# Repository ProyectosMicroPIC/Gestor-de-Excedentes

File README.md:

Con este Gestor de Excedentes completamente DIY podrás derivar tus excedentes fotovoltaicos a cualquier electrodoméstico (resistivo) que tengas en casa, aprovechando la energía sobrante de la mejor manera.

En el vídeo te explico cómo está hecho y cómo funciona.

https://youtu.be/Iet8Q6aDYok

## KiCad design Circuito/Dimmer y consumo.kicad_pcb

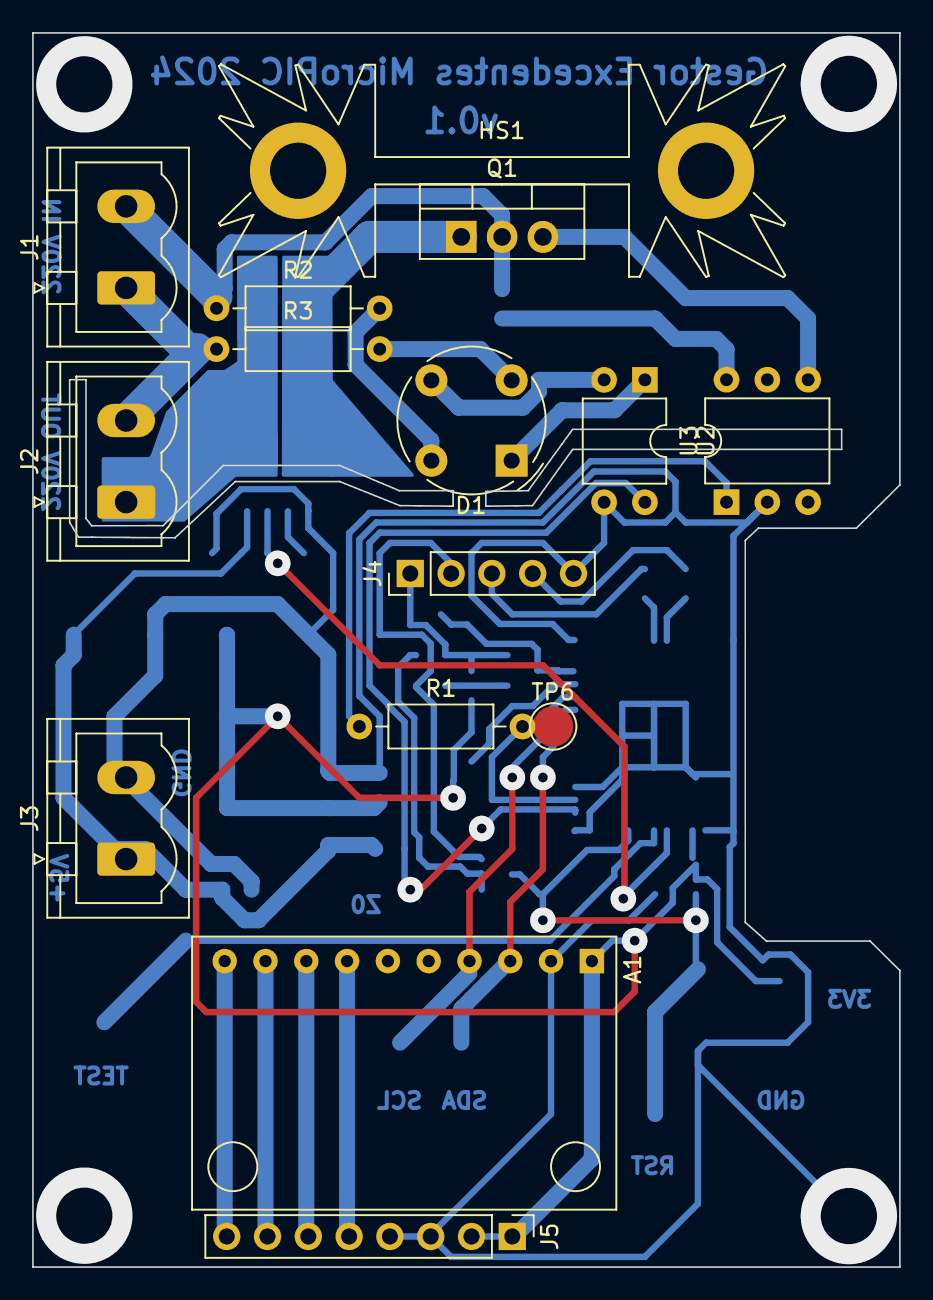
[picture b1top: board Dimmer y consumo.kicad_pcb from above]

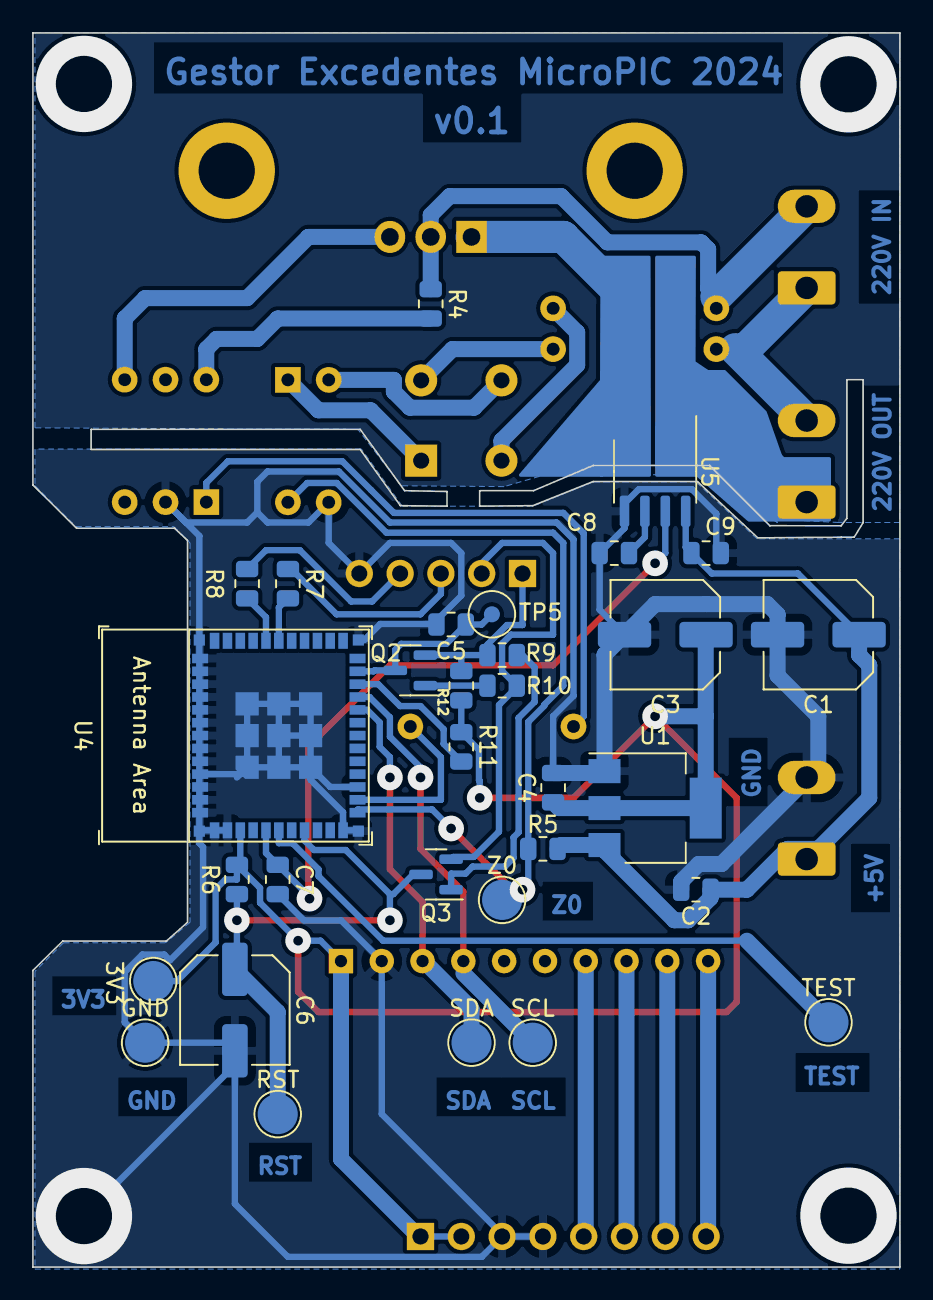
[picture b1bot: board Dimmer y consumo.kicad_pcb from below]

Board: 2 copper layers, 54.0 x 76.8 mm, 46 parts (31 on the bottom side), 36 nets.

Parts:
3V3: 3V3; TestPoint_Pad_D2.5mm
A1: ADS1115_ADC_Module; ADC1115_ADC_Module
C1, C3: 100uF; C_Elec_6.3x7.7
C2, C4, C5, C9: 100nF; R_0805_2012Metric
C6: 1uF; C_Elec_6.3x7.7
C7: 10nF; R_0805_2012Metric
C8: 1nF; R_0805_2012Metric
D1: B500R; Diode_Bridge_Round_D9.0mm
GND: GND; TestPoint_Pad_D2.5mm
HS1: Heatsink; Heatsink_Fischer_SK104-STCB_35x13mm__2xDrill3.5mm_ScrewM3
J1: 220Vac; PhoenixContact_MSTBVA_2,5_2-G-5,08_1x02_P5.08mm_Vertical
J2: Salida; PhoenixContact_MSTBVA_2,5_2-G-5,08_1x02_P5.08mm_Vertical
J3: 5V; PhoenixContact_MSTBVA_2,5_2-G-5,08_1x02_P5.08mm_Vertical
J4: Programación; PinHeader_1x05_P2.54mm_Vertical
J5: Analógicas; PinHeader_1x08_P2.54mm_Vertical
Q1: BTA16-600B; TO-220-3_Vertical
Q2: BC807; SOT-23
Q3: BC817; SOT-23
R1: 1K; R_Axial_DIN0207_L6.3mm_D2.5mm_P10.16mm_Horizontal
R2, R3: 30K 1/2W; R_Axial_DIN0207_L6.3mm_D2.5mm_P10.16mm_Horizontal
R4, R5: 1K; R_0805_2012Metric
R6, R9, R10, R11, R12: 10K; R_0805_2012Metric
R7, R8: 0; R_0805_2012Metric
RST: CHIP_PU; TestPoint_Pad_D2.5mm
SCL: SCL; TestPoint_Pad_D2.5mm
SDA: SDA; TestPoint_Pad_D2.5mm
TEST: Test1; TestPoint_Pad_D2.5mm
TP5: GPIO9; TestPoint_Pad_D2.5mm
TP6: Triac; TestPoint_Pad_D2.5mm
U1: LM1117DT-3.3; SOT-223-3_TabPin2
U2: PC817; DIP-4_W7.62mm
U3: MOC3021M; DIP-6_W7.62mm
U4: ESP32-C3-MINI-1
U5: ACS724LLCTR-10AB-S; SOIC-8_3.9x4.9mm_P1.27mm
Z0: Cruce0; TestPoint_Pad_D2.5mm

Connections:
+3V3: 3V3.1, A1.1 (VCC), C3.1, C4.1, J5.1, J5.2, R6.2, R11.1, R12.1, U1.2 (VO), U4.3 (3V3)
/CHIP_PU: C6.1, Q3.3 (C), R6.1, RST.1, U4.8 (EN/CHIP_PU)
/Cruce0: R5.1, U2.4, U4.12 (GPIO0/ADC1_CH0/XTAL_32K_P), Z0.1
/DTR: J4.1, Q2.2 (E), R9.2, R12.2
/RTS: J4.2, Q3.2 (E), R10.2
/SCL: A1.4 (SDA), SCL.1, U4.21 (GPIO7)
/SDA: A1.3 (SCL), SDA.1, U4.20 (GPIO6)
/Triac: R1.2, TP6.1, U4.13 (GPIO1/ADC1_CH1/XTAL_32K_N)
/U0RXD: J4.3, R7.1
/U0TXD: J4.4, R8.1
Consumo: C7.1, U4.5 (GPIO2/ADC1_CH2), U5.7 (VIOUT)
GND: A1.2 (GND), C1.2, C2.2, C3.2, C4.2, C5.2, C6.2, C7.2, C8.2, C9.2, GND.1, J3.2, J4.5, J5.3, J5.4, U1.1 (GND), U2.3, U3.2, U4.1 (GND), U4.2 (GND), U4.11 (GND), U4.14 (GND), U4.36 (GND), U4.37 (GND), U4.38 (GND), U4.39 (GND), U4.40 (GND), U4.41 (GND), U4.42 (GND), U4.43 (GND), U4.44 (GND), U4.45 (GND), U4.46 (GND), U4.47 (GND), U4.48 (GND), U4.49 (GND), U4.50 (GND), U4.51 (GND), U4.52 (GND), U4.53 (GND), U5.5 (GND)
unnamed: A1.7 (A0), J5.5
unnamed: A1.8 (A1), J5.6
unnamed: A1.9 (A2), J5.7
unnamed: A1.10 (A3), J5.8
unnamed: D1.1 (+), U2.1
unnamed: D1.3 (-), U2.2
unnamed: D1.2, R3.2
unnamed: D1.4, R2.2
unnamed: J1.1, J2.2, R3.1
unnamed: J1.2, Q1.2 (A2), R2.1, R4.1
unnamed: J2.1, U5.1 (IP+), U5.2 (IP+)
unnamed: Q1.1 (A1), U5.3 (IP-), U5.4 (IP-)
unnamed: Q1.3 (G), U3.4
unnamed: Q2.1 (B), R10.1
unnamed: C5.1, Q2.3 (C), TP5.1, U4.23 (GPIO9)
unnamed: Q3.1 (B), R9.1
unnamed: R1.1, U3.1
unnamed: R4.2, U3.6
unnamed: TEST.1, U4.6 (GPIO3/ADC1_CH3)
unnamed: R11.2, U4.22 (GPIO8)
unnamed: R7.2, U4.30 (GPIO20/U0RXD)
unnamed: R8.2, U4.31 (GPIO21/U0TXD)
unnamed: C8.1, U5.6 (FILTER)
VCC: C1.1, C2.1, C9.1, J3.1, R5.2, U1.3 (VI), U5.8 (VCC)

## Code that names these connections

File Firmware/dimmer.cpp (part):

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#define serial_activado

// Pinout
 uint8_t pinSalida; // Usamos el pin de TEST porque el pin 1 no va 1; // Pin GPIO1 que excitará al Triac
 uint8_t pinEntrada; // Pin GPIO0 para detectar los cruces por 0
 uint8_t pinAnalogico; // Pin GPIO4 entrada analógica para leer consumo
 uint8_t pinSCL;
 uint8_t pinSDA;

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

    pinMode(pinEntrada, INPUT);                   // Definimos el pin de entrada para la detección de cruces por 0
    pinMode(pinSalida, OUTPUT);                   // Definimos el pin de salida que excitará al Triac

    // Asignamos la función "deteccion0" a la interrupción por un flanco de subida en la entrada
    attachInterrupt(digitalPinToInterrupt(pinEntrada), dimmer::deteccion0, RISING);
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
  if (estado<=E_Calculando || estado == E_Encendido) {
    if (contadorPulsos==CicloDimmer && CicloDimmer<98) // llegados al punto de la onda en que queremos encender ...
      digitalWrite(pinSalida, true); // ... activa la salida del Triac 

    if (contadorPulsos==CicloDimmer+10) { // y un ciclo del reloj más tarde ...
      if (CicloDimmer>1)
        digitalWrite(pinSalida, false); // ... desactiva la salida del Triac 
      }
    if (contadorPulsos==vDimmerActivaDeteccion)
      // para detectar el próximo cruce por 0 es necesario activar la interrupción externa
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
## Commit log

2024-02-23 Circuito
    Esquemático y diseño de la PCB en Kicad
2024-02-23 Firmware
    Código para el ESP32 compilado con PlatformIO bajo Framework Arduino
